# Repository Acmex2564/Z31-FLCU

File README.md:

# Z31-FLCU
Reverse Engineering of the 300zx (Z31) Analog -> Digital Fuel Tank Gauge Converter Unit

This is a small, silver box located under the hatch of very late Z31s, or cars that have had the original, linear-slide Tank Gauge Sending Unit (TGSU) replaced with the late swing-arm style. 

Analog and digital cars used TGSUs with different resistance curves, to suit the needs of the gauge cluster. The linear-slide parts often demonstrated poor accuracy and high wear-out rates, and the swing arm parts are a commonly sought upgrade. However, Nissan did not produce the same two variants of the later part. Instead, all were produced with the resistance curve for the analog cluster, and if you ordered the replacement part for a digital car you recieved the analog swing-arm, with a small converter box that adjusted the levels to suit the digital cluster.

Now, 30 years later, these simple, hastily-produced boxes are both rare and often affected by corrosion. Their environmental seals are poor, and cases are made of steel in a car with notoriously poor weatherproofing. Perfect for rusting away!

This repository contains my attempt at determing the schematic and method of operation for this tiny circuit. Perhaps one day it will also contain replacement PCB details. 

The key players on the board are:

Zener diode for IC voltage supply (YUP, they removed the actual VR IC to save costs!)
Current limiting resistor to save the Zener
Filter and reservoir caps for the power supply side
Hitachi HA1813P Analog Voltage Comparator
Hitachi D789 NPN transistor
Second Zener diode limiting the voltage from the cluster on the fuel-level sub-gauge sense circuit

The actual function of this part is incredibly simple: at a main level reading of less than 3.6V (that is, more than approximately 1/4 tank) the sub level signal line is grounded, causing the cluster to disable the display. That's it.

Datasheets for the two Hitachi parts are located in the repository, because the datasheet for HA1813PS is difficult to find and I had already saved the other. 
Also found are images of the part in question, and it's wiring harness.

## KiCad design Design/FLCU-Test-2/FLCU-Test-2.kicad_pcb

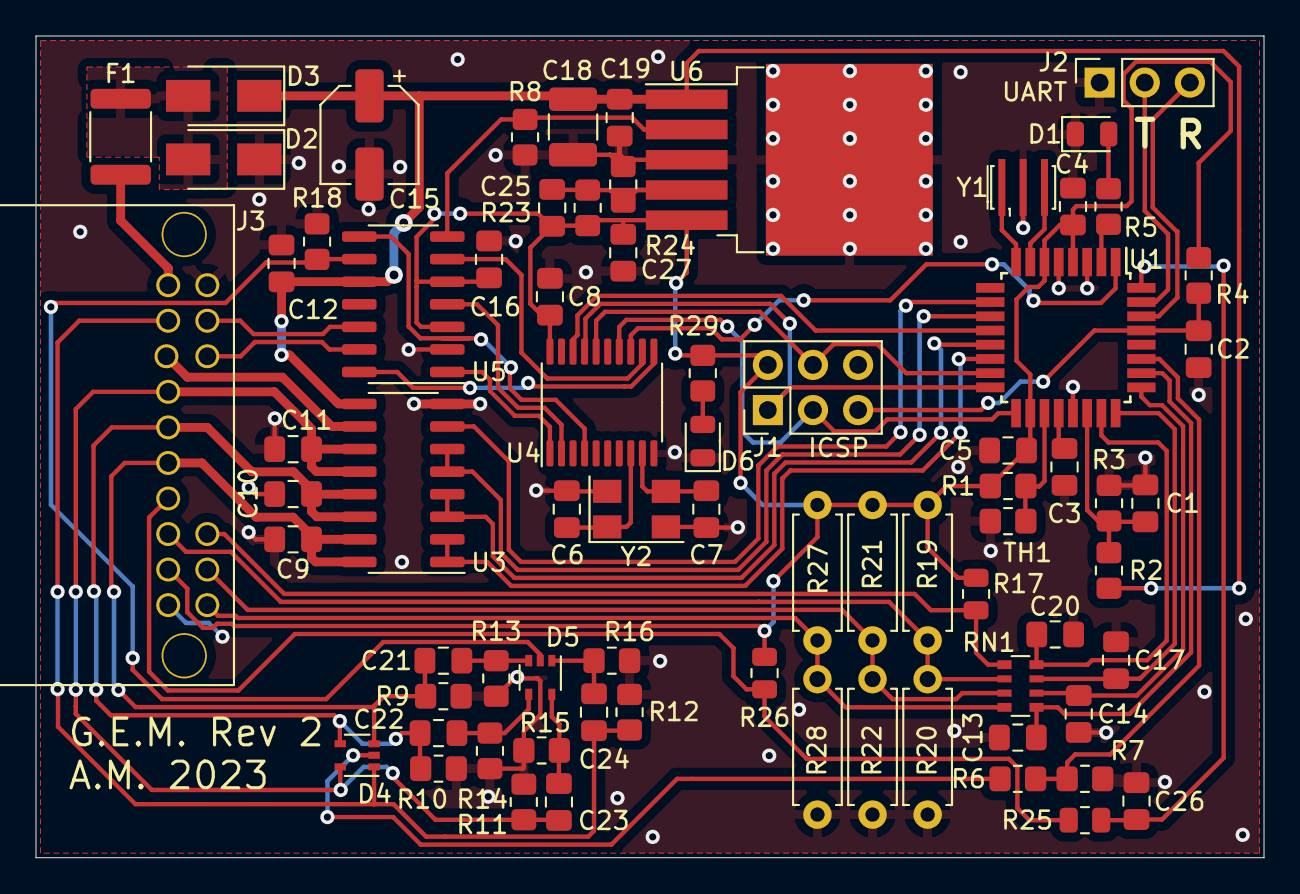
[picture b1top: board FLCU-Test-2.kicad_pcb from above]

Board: 2 copper layers, 69.1 x 46.2 mm, 75 parts (0 on the bottom side), 58 nets.

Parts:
C1, C2, C3, C13, C14, C17, C19, C20, C26: 100nF; C_0805_2012Metric_Pad1.18x1.45mm_HandSolder
C4, C5: 1uF; C_0805_2012Metric_Pad1.18x1.45mm_HandSolder
C6, C7: 20pF; C_0805_2012Metric_Pad1.18x1.45mm_HandSolder
C8, C12, C16, C21, C22, C23, C24: 100n; C_0805_2012Metric_Pad1.18x1.45mm_HandSolder
C9, C10, C11, C27: 22uF; C_0805_2012Metric_Pad1.18x1.45mm_HandSolder
C15: 22uF; CP_Elec_5x5.7
C18: 1u; C_1210_3225Metric_Pad1.33x2.70mm_HandSolder
C25: N/A; C_0805_2012Metric_Pad1.18x1.45mm_HandSolder
D1, D6: LED; LED_0805_2012Metric
D2: SMAJ18CAQ-13-F; D_SMA
D3: D; D_SMA
D4, D5: MMBD4448HCQW; SOT-353_SC-70-5
F1: SMD1812P050TF/30; R_1812_4532Metric
J1: ICSP; PinHeader_2x03_P2.54mm_Vertical
J2: UART; PinSocket_1x03_P2.54mm_Vertical
J3: 0348260160
R1, R3: 47k; R_0805_2012Metric_Pad1.20x1.40mm_HandSolder
R2: 150k; R_0805_2012Metric_Pad1.20x1.40mm_HandSolder
R4, R6, R7, R8, R9, R10, R11, R12, R13, R14, R15, R16, R18: 10k; R_0805_2012Metric_Pad1.20x1.40mm_HandSolder
R5, R29: 1K; R_0805_2012Metric_Pad1.20x1.40mm_HandSolder
R17: R; R_0805_2012Metric
R19, R20, R21, R22, R27, R28: R; R_Axial_DIN0207_L6.3mm_D2.5mm_P7.62mm_Horizontal
R23, R24: N/A; R_0805_2012Metric_Pad1.20x1.40mm_HandSolder
R25: 47k; R_0805_2012Metric
R26: 10k; R_0805_2012Metric
RN1: 47K; R_Array_Convex_4x0603
TH1: 47k; R_0805_2012Metric_Pad1.20x1.40mm_HandSolder
U1: ATmega328-AU; TQFP-32_7x7mm_P0.8mm
U3: ULN2003ADR; SOIC-16_3.9x9.9mm_P1.27mm
U4: MCP2515-xST; TSSOP-20_4.4x6.5mm_P0.65mm
U5: TJR1443; SO-14_3.9x8.65mm_P1.27mm
U6: NCV4276B; TO-263-5_TabPin3
Y1: 16MHz; Resonator_SMD_Murata_CSTxExxV-3Pin_3.0x1.1mm_HandSoldering
Y2: 8MHz; Crystal_SMD_5032-4Pin_5.0x3.2mm

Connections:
+5V: C4.2, C5.1, C8.2, C16.2, C25.1, C27.1, J1.2, J3.15, R1.1, R4.1, R17.1, R19.1, R21.1, R23.1, R26.1, R27.1, R29.1, U1.4 (VCC), U1.6 (VCC), U1.18 (AVCC), U4.20 (VDD), U5.3 (Vcc), U5.5 (Vio), U6.5 (OUT)
+12V: C12.2, C15.1, C18.1, C19.1, D3.1 (K), R2.1, U3.9 (COM), U5.10 (Vbat), U6.1 (IN)
+12V_BATTERY: F1.2, J3.7
+12V_IGN: C24.1, D4.1 (A), J3.8, R12.1
/A1_In: J3.6, R27.2, R28.1, RN1.4 (R4.1)
/A2_In: J3.5, R21.2, R22.1, RN1.3 (R3.1)
/A3_In: J3.14, R19.2, R20.1, RN1.2 (R2.1)
/A4_In: J3.4, R17.2, RN1.1 (R1.1)
/CAN_EN: U4.12 (~RX0BF), U5.6 (EN)
/CAN_ERR: U4.4 (~TX0RTS), U5.8 (~ERR)
/CAN_RX: U4.2 (RXCAN), U5.4 (RXCAN)
/CAN_STB: U4.11 (~RX1BF), U5.14 (~STB_N)
/CAN_TX: U4.1 (TXCAN), U5.1 (TXCAN)
/D1_INT_In: J3.13, R25.2, R26.2
/D4: U1.10 (PD6), U3.7 (I7)
/Extra-Out: J3.9, U3.10 (O7)
/Low-Level-Warning-Out: C11.1, C23.1, D4.5 (A), J3.10, R11.1, U3.11 (O6), U3.12 (O5)
/Main-Level-Out: C10.1, C22.1, D4.4 (A), J3.11, R10.1, U3.13 (O4), U3.14 (O3)
/Module-Temperature: R1.2, TH1.1, U1.19 (ADC6)
/Module_Voltage: C1.2, R2.2, R3.1, U1.22 (ADC7)
/POSTFUSE: D2.2 (A2), D3.2 (A), F1.1
/PWM1: U1.13 (PB1), U3.3 (I3), U3.4 (I4)
/PWM2: U1.11 (PD7), U3.5 (I5), U3.6 (I6)
/PWM3: U1.14 (PB2), U3.1 (I1), U3.2 (I2)
/Spare-Analog: C20.2, RN1.8 (R1.2), U1.23 (PC0)
/Sub-Level-Out: C9.1, C21.1, D4.3 (A), J3.12, R9.1, U3.15 (O2), U3.16 (O1)
/VREG_INH: R8.1, U5.7 (INH), U6.2 (~INH)
/Wake_Pulse: D5.2 (K), R18.1, U5.9 (WAKE)
/Wake_Sense: R6.2, R7.1, U1.27 (PC4)
CAN_CS: U1.12 (PB0), U4.18 (~CS)
CAN_H: J3.3, U5.13 (CANH)
CAN_INT: U1.1 (PD3), U4.13 (~INT)
CAN_L: J3.2, U5.12 (CANL)
EXT_INT: C26.2, R25.1, U1.32 (PD2)
GND: C1.1, C2.1, C3.2, C4.1, C5.2, C6.2, C7.2, C8.1, C9.2, C10.2, C11.2, C12.1, C13.1, C14.1, C15.2, C16.1, C17.1, C18.2, C19.2, C20.1, C26.1, C27.2, D1.1 (K), D2.1 (A1), D6.1 (K), J1.6, J2.1, J3.1, J3.16, R3.2, R7.2, R8.2, R9.2, R10.2, R11.2, R12.2, R13.2, R14.2, R15.2, R16.2, R18.2, R20.2, R22.2, R24.2, R28.2, TH1.2, U1.3 (GND), U1.5 (GND), U1.21 (GND), U3.8 (GND), U4.10 (VSS), U5.2 (GND), U6.3 (GND), Y1.2, Y2.2, Y2.4
Low-Level-Warning: C17.2, RN1.7 (R2.2), U1.24 (PC1)
MISO: J1.1, U1.16 (PB4), U4.17 (SO)
MOSI: J1.4, U1.15 (PB3), U4.16 (SI)
Main-Lvl: C13.2, RN1.5 (R4.2), U1.26 (PC3)
unnamed: C3.1, U1.20 (AREF)
unnamed: C6.1, U4.8 (OSC2), Y2.1
unnamed: C7.1, U4.9 (OSC1), Y2.3
unnamed: C21.2, D5.3 (A), R13.1
unnamed: C22.2, D5.4 (A), R14.1
unnamed: C23.2, D5.5 (A), R15.1
unnamed: C24.2, D5.1 (A), R16.1
unnamed: C25.2, R23.2, R24.1, U6.4 (VA)
unnamed: D1.2 (A), R5.2
unnamed: D4.2 (K), R6.1
unnamed: D6.2 (A), R29.2
unnamed: R5.1, U1.2 (PD4)
unnamed: U1.7 (XTAL1/PB6), Y1.3
unnamed: U1.8 (XTAL2/PB7), Y1.1
RESET: C2.2, J1.5, R4.2, U1.29 (~RESET/PC6)
RXD: J2.3, U1.30 (PD0)
SCK: J1.3, U1.17 (PB5), U4.14 (SCK)
Sub-Level: C14.2, RN1.6 (R3.2), U1.25 (PC2)
TXD: J2.2, U1.31 (PD1)

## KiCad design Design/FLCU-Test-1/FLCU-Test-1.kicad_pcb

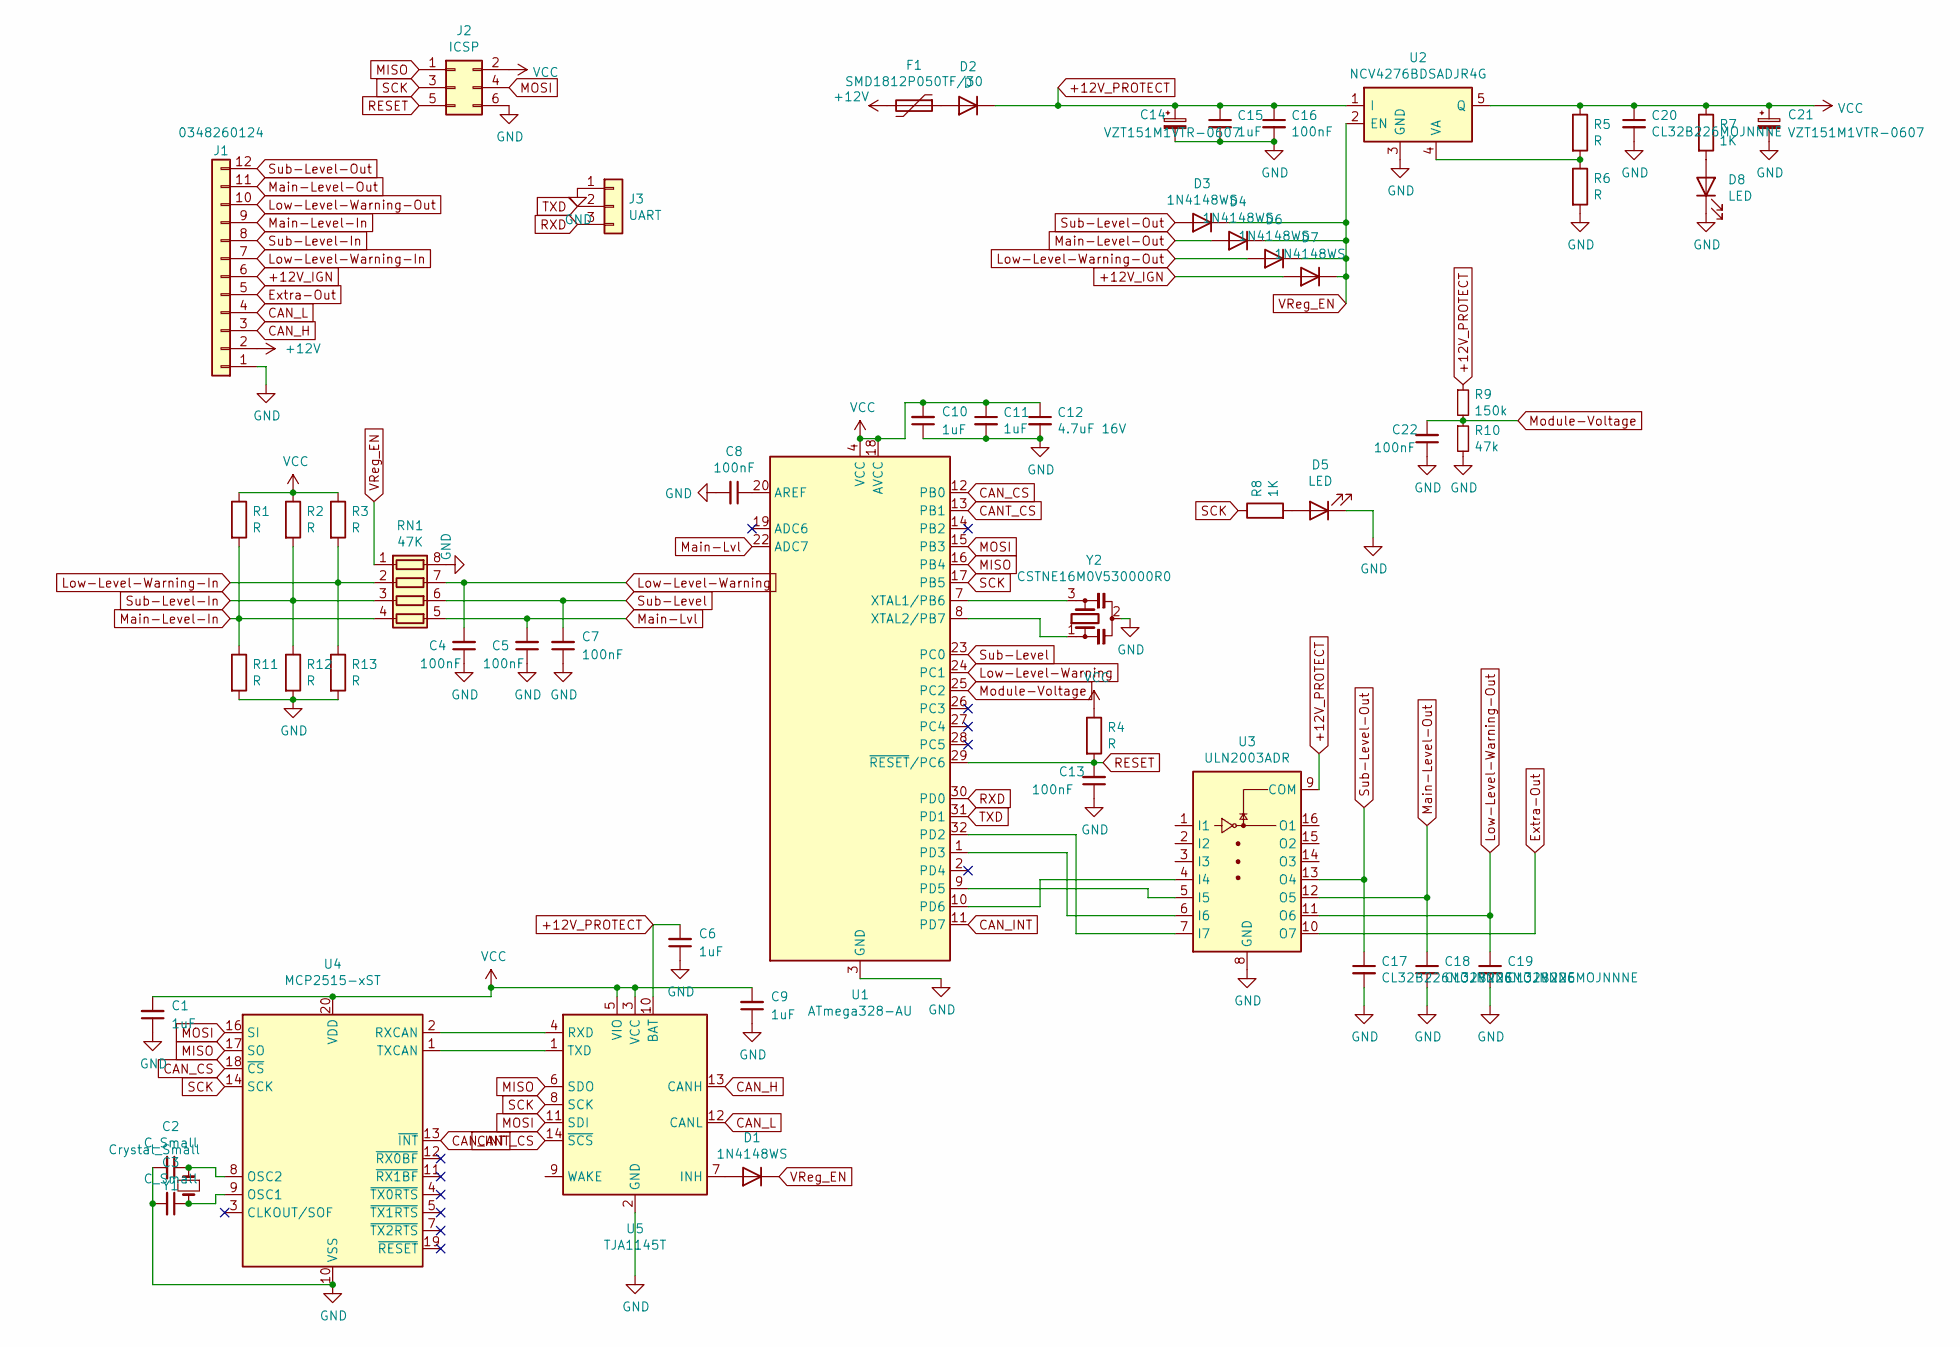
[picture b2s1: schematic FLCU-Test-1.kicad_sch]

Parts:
C1, C6, C9, C10, C11, C15: 1uF; C_0603_1608Metric
C2, C3: C_Small; C_0603_1608Metric
C4, C5, C7, C8, C13, C16, C22: 100nF; C_0603_1608Metric
C12: 4.7uF 16V; C_0805_2012Metric
C14, C21: VZT151M1VTR-0607; CP_Elec_6.3x7.7
C17, C18, C19: CL32B226MOJNNNE; C_0805_2012Metric_Pad1.18x1.45mm_HandSolder
C20: CL32B226MOJNNNE; C_1210_3225Metric
D1, D3, D4, D6, D7: 1N4148WS; D_SOD-323F
D2: D; D_1210_3225Metric_Pad1.42x2.65mm_HandSolder
D5, D8: LED; LED_0805_2012Metric
F1: SMD1812P050TF/30; R_1812_4532Metric
J1: 0348260124; 034826012-
J2: ICSP; PinHeader_2x03_P2.54mm_Vertical
J3: UART; PinSocket_1x03_P2.54mm_Vertical
R1, R2, R3, R11, R12, R13: R; R_Axial_DIN0207_L6.3mm_D2.5mm_P7.62mm_Horizontal
R4, R5, R6: R; R_0603_1608Metric
R7, R8: 1K; R_0603_1608Metric
R9: 150k; R_0805_2012Metric_Pad1.20x1.40mm_HandSolder
R10: 47k; R_0805_2012Metric_Pad1.20x1.40mm_HandSolder
RN1: 47K; R_Array_Convex_4x0603
U1: ATmega328-AU; TQFP-32_7x7mm_P0.8mm
U2: NCV4276BDSADJR4G; TO-263-5_TabPin3
U3: ULN2003ADR; SOIC-16_3.9x9.9mm_P1.27mm
U4: MCP2515-xST; TSSOP-20_4.4x6.5mm_P0.65mm
U5: TJA1145T; SOIC-14_3.9x8.7mm_P1.27mm
Y1: Crystal_Small; Crystal_HC18-U_Vertical
Y2: CSTNE16M0V530000R0; Resonator_SMD_muRata_CSTxExxV-3Pin_3.0x1.1mm

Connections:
+12V: F1.2, J1.2
+12V_IGN: D7.2 (A), J1.6
+12V_PROTECT: C6.2, C14.1, C15.1, C16.1, D2.1 (K), R9.1, U2.1 (I), U3.9 (COM), U5.10 (BAT)
CANT_CS: U1.13 (PB1), U5.14 (~SCS)
CAN_CS: U1.12 (PB0), U4.18 (~CS)
CAN_H: J1.3, U5.13 (CANH)
CAN_INT: U1.11 (PD7), U4.13 (~INT)
CAN_L: J1.4, U5.12 (CANL)
Extra-Out: J1.5, U3.10 (O7)
GND: C1.1, C2.2, C3.2, C4.1, C5.1, C6.1, C7.1, C8.2, C9.1, C10.1, C11.2, C12.2, C13.1, C14.2, C15.2, C16.2, C17.2, C18.2, C19.2, C20.2, C21.2, C22.1, D5.1 (K), D8.1 (K), J1.1, J2.6, J3.1, R6.2, R10.2, R11.2, R12.2, R13.2, RN1.8 (R1.2), U1.3 (GND), U1.5 (GND), U1.21 (GND), U2.3 (GND), U3.8 (GND), U4.10 (VSS), U5.2 (GND), Y2.2
Low-Level-Warning: C4.2, RN1.7 (R2.2), U1.24 (PC1)
Low-Level-Warning-In: J1.7, R3.2, R13.1, RN1.2 (R2.1)
Low-Level-Warning-Out: C19.1, D6.2 (A), J1.10, U3.11 (O6)
MISO: J2.1, U1.16 (PB4), U4.17 (SO), U5.6 (SDO)
MOSI: J2.4, U1.15 (PB3), U4.16 (SI), U5.11 (SDI)
Main-Level-In: J1.9, R1.2, R11.1, RN1.4 (R4.1)
Main-Level-Out: C18.1, D4.2 (A), J1.11, U3.12 (O5)
Main-Lvl: C5.2, RN1.5 (R4.2), U1.22 (ADC7)
Module-Voltage: C22.2, R9.2, R10.1, U1.25 (PC2)
unnamed: C2.1, U4.8 (OSC2), Y1.1
unnamed: C3.1, U4.9 (OSC1), Y1.2
unnamed: C8.1, U1.20 (AREF)
unnamed: D1.2 (A), U5.7 (INH)
unnamed: D2.2 (A), F1.1
unnamed: D5.2 (A), R8.2
unnamed: D8.2 (A), R7.2
unnamed: R5.2, R6.1, U2.4 (VA)
unnamed: U1.1 (PD3), U3.6 (I6)
unnamed: U1.7 (XTAL1/PB6), Y2.3
unnamed: U1.8 (XTAL2/PB7), Y2.1
unnamed: U1.9 (PD5), U3.5 (I5)
unnamed: U1.10 (PD6), U3.4 (I4)
unnamed: U1.32 (PD2), U3.7 (I7)
unnamed: U4.1 (TXCAN), U5.1 (TXD)
unnamed: U4.2 (RXCAN), U5.4 (RXD)
RESET: C13.2, J2.5, R4.2, U1.29 (~RESET/PC6)
RXD: J3.3, U1.30 (PD0)
SCK: J2.3, R8.1, U1.17 (PB5), U4.14 (SCK), U5.8 (SCK)
Sub-Level: C7.2, RN1.6 (R3.2), U1.23 (PC0)
Sub-Level-In: J1.8, R2.2, R12.1, RN1.3 (R3.1)
Sub-Level-Out: C17.1, D3.2 (A), J1.12, U3.13 (O4)
TXD: J3.2, U1.31 (PD1)
VCC: C1.2, C9.2, C10.2, C11.1, C12.1, C20.1, C21.1, J2.2, R1.1, R2.1, R3.1, R4.1, R5.1, R7.1, U1.4 (VCC), U1.6 (VCC), U1.18 (AVCC), U2.5 (Q), U4.20 (VDD), U5.3 (VCC), U5.5 (VIO)
VReg_EN: D1.1 (K), D3.1 (K), D4.1 (K), D6.1 (K), D7.1 (K), RN1.1 (R1.1), U2.2 (EN)

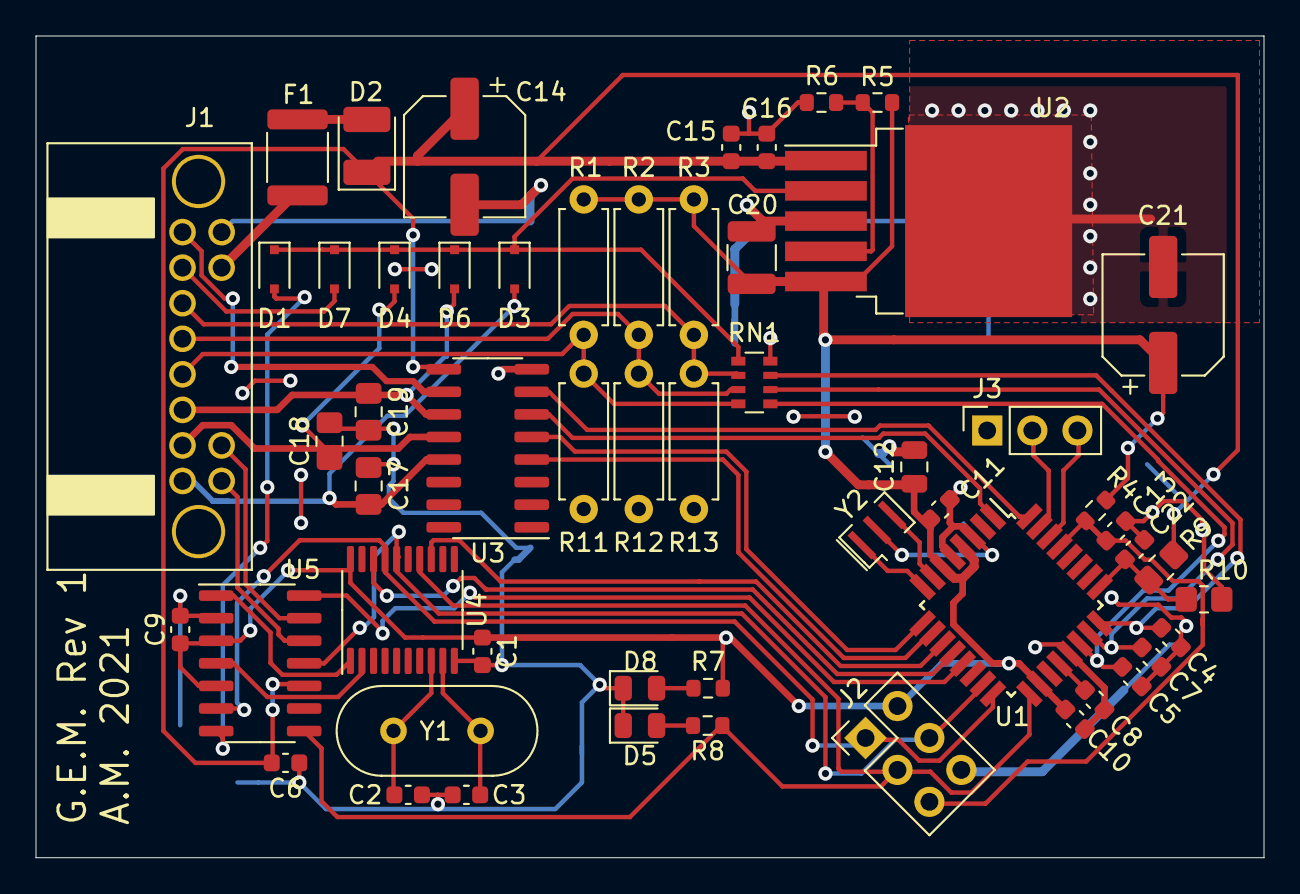
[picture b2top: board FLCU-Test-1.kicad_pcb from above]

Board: 2 copper layers, 69.1 x 46.2 mm, 55 parts (0 on the bottom side), 44 nets.

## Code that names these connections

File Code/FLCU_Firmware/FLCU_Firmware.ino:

//Libaries
#include <mcp_can.h>

//Pin assignments
#define MAIN_IN A7
#define MAIN_OUT 5

#define SUB_IN A0
#define SUB_OUT 6

#define LL_IN A1
#define LL_OUT 3

#define AUX_OUT 2

#define MODULE_VOLTAGE A2

#define LED 13

#define CAN_INT 7
#define CAN_CS 8
#define CANT_CS 9

#define HIST_ARRAY_SIZE 5

#define NUM_MAIN 20
#define NUM_MAIN_OUT 21
#define NUM_SUB 10

#define SERIAL_SPEED 9600




unsigned long timeCurrent = 0;
const unsigned int intervalReadLevels = 200;
unsigned long timeLastRead = 0;
const unsigned int intervalSerialStatus = 2000;
unsigned long timeLastStatus = 0;
const unsigned int intervalBlink = 1000;
unsigned long timeLastBlink;

const unsigned int intervalCan = 1000;
unsigned long timeLastCan = 0;

MCP_CAN CAN0(CAN_CS);
const unsigned long int idPacketLevelOut = 0x720;
const uint8_t canTxLen = 6;
uint8_t canTxBuf[8];
byte canSendStat; 

//Calibration Constants

// Module Voltage
// 150k and 47k
const float divVolts = (150.0+47.0) / 47.0 ;

// Fuel level senders are configured as voltage dividers
// Here we have two, configured as "Main" and "Sub"
// Variables "t_" represent the resistor value on the top side of the divider
// Variables "b_Min" and "b_Max" represent the range of expected resistance values in the tank
// All resistance values are times 100 to keep the math as integers
int tMain = 110;
int tSub = 235;

int rMain[NUM_MAIN] = {
  80, 72,
  66, 61,
  56, 51,
  45, 42, 
  38, 34,
  31, 29, 
  26, 23,
  19, 14,
  10, 5,
  3, 1
};


int rSub[NUM_SUB] = {
  3, 6,
  12, 19,
  30, 49,
  96, 127,
  273, 275
};

int oMain[NUM_MAIN_OUT] = {
  13, 15, 
  17, 22,
  28, 34, 
  43, 52,
  62, 69,
  80, 96,
  112, 122, 
  139, 157,
  170, 188, 
  211, 230, 
  246
};

int oSub[NUM_SUB]= {
  13, 21,
  29, 47,
  107, 180,
  232, 237,
  243, 246
};

int levelPrevPos = 0;

void setup() {
  // put your setup code here, to run once:

pinMode(MAIN_IN, INPUT);
pinMode(SUB_IN, INPUT);
pinMode(LL_IN, INPUT);
pinMode(MODULE_VOLTAGE, INPUT);
pinMode(CAN_INT, INPUT);

pinMode(MAIN_OUT, OUTPUT);
pinMode(SUB_OUT, OUTPUT);
pinMode(LL_OUT, OUTPUT);
pinMode(AUX_OUT, OUTPUT);
pinMode(LED, OUTPUT);
pinMode(CAN_CS, OUTPUT);
pinMode(CANT_CS, OUTPUT);

Serial.begin(SERIAL_SPEED);

//TCCR0B = TCCR0B & B11111000 | B00000010; // for PWM frequency of 7812.50 Hz
TCCR2B = TCCR2B & B11111000 | B00000010; // for PWM frequency of 3921.16 Hz
  writeLevel(NUM_MAIN_OUT, oMain, readLevel(NUM_MAIN, rMain, false, tMain, analogRead(MAIN_IN)), MAIN_OUT );
  writeLevel(NUM_SUB, oSub, readLevel(NUM_SUB, rSub, true, tSub, analogRead(SUB_IN)), SUB_OUT );

//  digitalWrite(CAN_RESET, HIGH);
  //delay(50);
  digitalWrite(CANT_CS, LOW);
  int canstat = CAN0.begin(MCP_ANY, CAN_500KBPS, MCP_8MHZ);
  if (canstat == CAN_OK)
  {
    Serial.println("MCP2515 Initialized Successfully!");
  }
  else
  {
    Serial.print("Error Initializing MCP2515..."); Serial.println(canstat);
  }
  // can controller into normal mode
  CAN0.setMode(MCP_NORMAL);



}

void loop() {
  // put your main code here, to run repeatedly:

  timeCurrent = millis();

  if (timeCurrent - timeLastRead > intervalReadLevels)
  {

  digitalWrite(LED, HIGH);
  writeLevel(NUM_MAIN_OUT, oMain, readLevel(NUM_MAIN, rMain, false, tMain, analogRead(MAIN_IN)), MAIN_OUT );
  
  
  writeLevel(NUM_SUB, oSub, readLevel(NUM_SUB, rSub, true, tSub, analogRead(SUB_IN)), SUB_OUT );
  timeLastRead = timeCurrent;
  digitalWrite(LED, LOW);
  }

  if (timeCurrent - timeLastStatus > intervalSerialStatus)
  {
      
    Serial.println("Heartbeat");
    Serial.print("Module Volts:"); Serial.println((analogRead(MODULE_VOLTAGE) * 5.0 / 1023.0) * divVolts);
    Serial.print("Supply Volts:"); Serial.println(readVcc());
    Serial.print(" Main Level (Gal): "); Serial.println(readLevel(NUM_MAIN, rMain, false, tMain, analogRead(MAIN_IN)));
    Serial.print(" Main Level (PWM): "); Serial.println(writeLevel(NUM_MAIN_OUT, oMain, readLevel(NUM_MAIN, rMain, false, tMain, analogRead(MAIN_IN)), MAIN_OUT ));
    Serial.print(" Sub Level (Gal): "); Serial.println(readLevel(NUM_SUB, rSub, true, tSub, analogRead(SUB_IN)));
    Serial.print(" Sub Level (PWM): "); Serial.println(writeLevel(NUM_SUB, oSub, readLevel(NUM_SUB, rSub, true, tSub, analogRead(SUB_IN)), SUB_OUT ));
    timeLastStatus = timeCurrent;
  }
  

  if (timeCurrent - timeLastCan > intervalCan)
  {
    canTxBuf[0] = readLevel(NUM_MAIN, rMain, false, tMain, analogRead(MAIN_IN)) * 10;
    canTxBuf[1] = readLevel(NUM_SUB, rSub, true, tSub, analogRead(SUB_IN)) * 10;
    canTxBuf[2] = 0xFF;
    canTxBuf[3] = 0xFF;
    canTxBuf[4] = 0xFF;
    canTxBuf[5] = 0xFF;
    canSendStat = CAN0.sendMsgBuf(idPacketLevelOut, 0, canTxLen, canTxBuf);
    if (canSendStat == CAN_OK){
      Serial.println("CanOK");
    }
    else {
      Serial.print("CanErr: "); Serial.println(canSendStat);
    }
    timeLastCan = timeCurrent;
    
  }

  
  

}

long readVcc() {
  long result;
  // Read 1.1V reference against AVcc
  ADMUX = _BV(REFS0) | _BV(MUX3) | _BV(MUX2) | _BV(MUX1);
  delay(2); // Wait for Vref to settle
  ADCSRA |= _BV(ADSC); // Convert
  while (bit_is_set(ADCSRA,ADSC));
  result = ADCL;
  result |= ADCH<<8;
  result = 1125300L / result; // Back-calculate AVcc in mV
  return result;
}

int writeLevel(int numElem, int * table, float level, int pinOut) {
  int index;
  int result;

  index = constrain(floor(level), 0, numElem-1);

  level = floor(level*100.0);
  level = (int)level;
  //Serial.print("  Index: "); Serial.println(index);
  
  
  
  result = map(level, index*100, (index+1)*100, table[index], table[index+1] );
  analogWrite(pinOut, result);
  return result;
  //Serial.print("  PWM: "); Serial.println(result);
};

float readLevel(int numElem, int * table, bool reverse, int rTop, int reading) {
  float reading2;
  float result;
  int index;

  //convert adc reading to resistance
  reading2 = constrain(reading, 1, 1023);
  reading2 = rTop / (((1024.0)/(reading))-1);
  //Serial.print("  Reading (Ohm): "); Serial.println(reading2);
  
  //cycle through lookup table until value is greater than (normal) or less than (reverse)the current table value
  for (index = 0; index <= numElem - 1; index++) 
  {
    //Serial.println(index);
    if ((!reverse && reading2 >= table[index]) || ( reverse && reading2 <= table[index])) 
    {
      break;
    }   
  }
  
  //linear interpolation between last and next value
  if (index < numElem-1) 
  {
    result = float(index-1) + ((reading2 - float(table[index-1])) * ((float(index) - float(index-1))/float(table[index] - table[index-1])));
  }
  else
  {
    result = index;
  }
  //Serial.print("  Level   (Gal): "); Serial.println(result);

  return result;
}

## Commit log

2021-02-01 First draft of PCB Revised functional description
2022-09-11 Add design files to repository
2022-09-29 Include arduino sketch
2023-05-21 Tentative Completion of Rev2 of FLCU / GEM - Switch to TJR1443 CAN transceiver - Smaller, more modern crystal for MCP2515 - Pulse-forming network to use sleep/wake functionality of TJR1443 - Switch f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
    This revision was done to correct some sleep/wake issues with Rev1, and to support it's use as a boost controller (with different FW)
    - Out - PWM Boost Control Solenoid
    - Out - PWM Electric Water Pump (Intercooler)
    - Out - Intercooler Fan Relay
    - DIn - Turbine speed
    - AIn - Manifold Pressure
2023-05-21 Updated firmware for Rev1 FLCU (Serial printout and sleep/wake tweaks)
2025-01-17 GEM Rev2 (formerly FLCU Rev2) design & layout complete.
